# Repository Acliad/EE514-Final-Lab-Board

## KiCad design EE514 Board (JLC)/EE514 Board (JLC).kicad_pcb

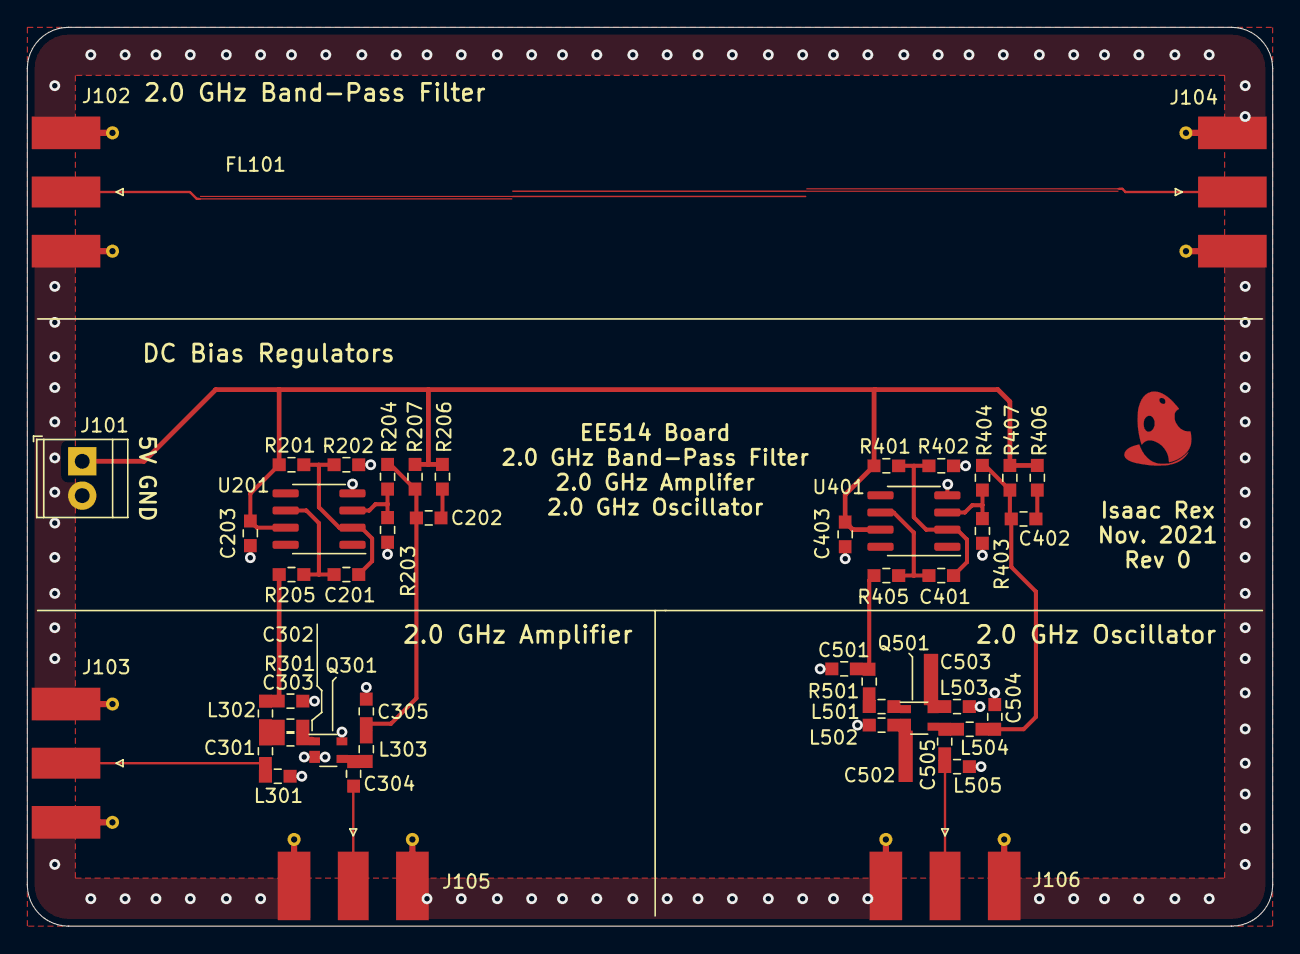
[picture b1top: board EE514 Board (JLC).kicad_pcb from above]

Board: 4 copper layers, 92.2 x 66.5 mm, 51 parts (0 on the bottom side), 27 nets.

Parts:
C201, C202, C401, C402: 12nF; C_0603_1608Metric_Pad0.98x0.95mm_HandSolder
C203, C403: 0.1uF; C_0603_1608Metric_Pad0.98x0.95mm_HandSolder
C301: 4.7pF; C_0603_1608Metric_Pad0.98x0.95mm_HandSolder
C302, C303, C305, C501, C504: 7.5pF; C_0603_1608Metric_Pad0.98x0.95mm_HandSolder
C304: 6.8pF; C_0603_1608Metric_Pad0.98x0.95mm_HandSolder
C502, C503: 1.7pF; C_1.7pF_Microstrip
C505: 3pF; C_0603_1608Metric_Pad0.98x0.95mm_HandSolder
FL101: BPF-2; Filter_2.0GHz_Bandpass_Edge-Coupled_JLC
J101: Screw_Terminal_01x02; TerminalBlock_TE_282834-2_1x02_P2.54mm_Horizontal
J102, J103, J104, J105, J106: SMA; SMA_Molex_73251-1153_EdgeMount_Horizontal
L301: 1.3nH; L_0603_1608Metric_Pad0.98x0.95mm_HandSolder
L302, L502, L503, L504: 18nH; L_0603_1608Metric_Pad0.98x0.95mm_HandSolder
L303: 1.8nH; L_0603_1608Metric_Pad0.98x0.95mm_HandSolder
L501: 6.2nH; L_0603_1608Metric_Pad0.98x0.95mm_HandSolder
L505: 2.2nH; L_0603_1608Metric_Pad0.98x0.95mm_HandSolder
Q301, Q501: BFP620; SOT-343_2.0x1.25mm_P1.3mm
R201, R401: 1.5k; R_0603_1608Metric_Pad0.98x0.95mm_HandSolder
R202, R402: 470; R_0603_1608Metric_Pad0.98x0.95mm_HandSolder
R203, R403: 11k; R_0603_1608Metric_Pad0.98x0.95mm_HandSolder
R204, R404: 7.5k; R_0603_1608Metric_Pad0.98x0.95mm_HandSolder
R205, R405: 3.3k; R_0603_1608Metric_Pad0.98x0.95mm_HandSolder
R206, R406: 18; R_0603_1608Metric_Pad0.98x0.95mm_HandSolder
R207, R407: 75; R_0603_1608Metric_Pad0.98x0.95mm_HandSolder
R301: 1; R_0603_1608Metric_Pad0.98x0.95mm_HandSolder
R501: 200; R_0603_1608Metric_Pad0.98x0.95mm_HandSolder
U201, U401: TLC2201; SOIC-8_3.9x4.9mm_P1.27mm

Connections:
+5V: C203.2, C403.2, J101.1, R201.1, R206.1, R207.1, R401.1, R406.1, R407.1, U201.7, U401.7
/Amplifier/RF_IN: C301.2, J103.1, L301.1
/Amplifier/RF_OUT: C304.1, J105.1
/Amplifier/V_BIAS_BASE: C302.2, L302.2, R205.1
/Amplifier/V_BIAS_COLLECTOR: C202.1, C305.2, L303.2, R204.1, R207.2
/Oscillator/RF_OUT: C505.1, J106.1, L505.1
/Oscillator/V_BASE_BIAS: C501.2, R405.1, R501.2
/Oscillator/V_BASE_COLLECTOR: C402.1, C504.2, L504.2, R404.1, R407.2
GND: C203.1, C302.1, C305.1, C403.1, C501.1, C504.1, J101.2, J102.2, J103.2, J104.2, J105.2, J106.2, L301.2, L502.2, L503.2, L505.2, Q301.2, Q301.4, R202.2, R203.2, R402.2, R403.2, U201.4, U401.4
unnamed: C201.1, R205.2, U201.6
unnamed: C201.2, R201.2, R202.1, U201.2
unnamed: C202.2, R206.2
unnamed: C301.1, C303.2, L302.1, R301.2
unnamed: C303.1, Q301.1, R301.1
unnamed: C304.2, L303.1, Q301.3
unnamed: C401.1, R405.2, U401.6
unnamed: C401.2, R401.2, R402.1, U401.2
unnamed: C402.2, R406.2
unnamed: C502.1, L502.1, Q501.2
unnamed: C503.1, L503.1, Q501.4
unnamed: C505.2, L504.1, Q501.3
unnamed: FL101.1, J102.1
unnamed: FL101.2, J104.1
unnamed: L501.1, R501.1
unnamed: L501.2, Q501.1
unnamed: R203.1, R204.2, U201.3
unnamed: R403.1, R404.2, U401.3

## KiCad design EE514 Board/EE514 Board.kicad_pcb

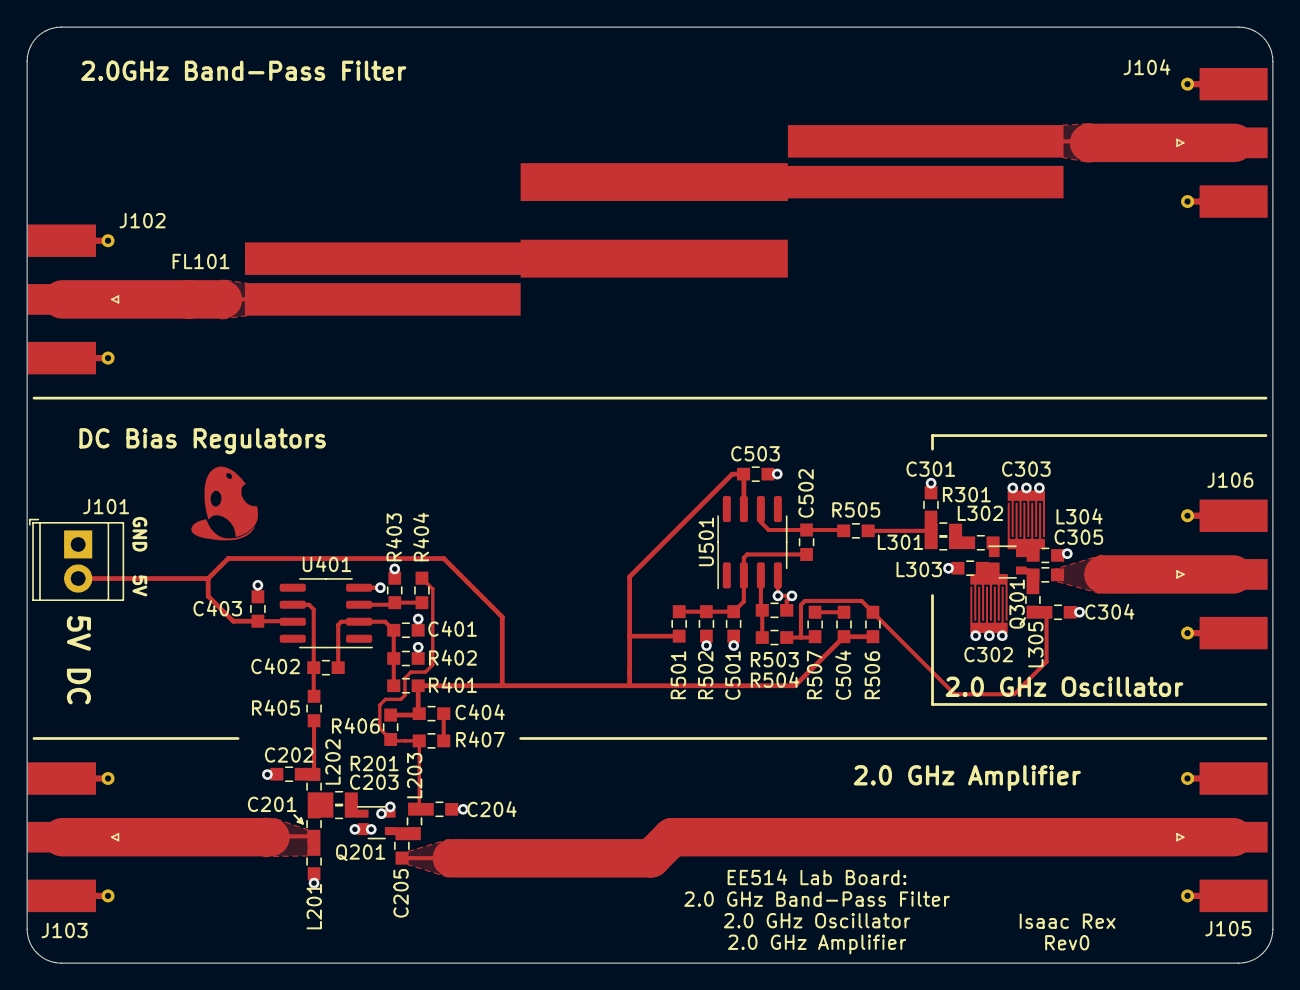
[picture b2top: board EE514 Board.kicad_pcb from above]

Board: 2 copper layers, 93.0 x 69.9 mm, 53 parts (0 on the bottom side), 27 nets.

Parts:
C201: 2.2pF; C_0603_1608Metric_Pad0.98x0.95mm_HandSolder
C202, C203, C204, C301, C304: 7.5pF; C_0603_1608Metric_Pad0.98x0.95mm_HandSolder
C205: 3.9pF; C_0603_1608Metric_Pad0.98x0.95mm_HandSolder
C302, C303: 1pF; C_1pF_Interdigital
C305: 3pF; C_0603_1608Metric_Pad0.98x0.95mm_HandSolder
C401, C403, C501, C503: 0.1nF; C_0603_1608Metric_Pad0.98x0.95mm_HandSolder
C402, C404, C502, C504: 12nF; C_0603_1608Metric_Pad0.98x0.95mm_HandSolder
FL101: BPF-2; Filter_2.0GHz_Bandpass_Edge-Coupled
J101: Screw_Terminal_01x02; TerminalBlock_TE_282834-2_1x02_P2.54mm_Horizontal
J102, J103, J104, J105, J106: SMA; SMA_Molex_73251-1153_EdgeMount_Horizontal
L201: 2.2nH; L_0603_1608Metric_Pad0.98x0.95mm_HandSolder
L202, L301, L303, L304: 18nH; L_0603_1608Metric_Pad0.98x0.95mm_HandSolder
L203: 3.9nH; L_0603_1608Metric_Pad0.98x0.95mm_HandSolder
L302: 7.5nH; L_0603_1608Metric_Pad0.98x0.95mm_HandSolder
L305: 8.2nH; L_0603_1608Metric_Pad0.98x0.95mm_HandSolder
Q201: BFP620; SOT-343_2.0x1.25mm_P1.3mm
Q301: BPF620; SOT-343_2.0x1.25mm_P1.3mm
R201: 1.5; R_0603_1608Metric_Pad0.98x0.95mm_HandSolder
R301: 150; R_0603_1608Metric_Pad0.98x0.95mm_HandSolder
R401, R501: 1.5k; R_0603_1608Metric_Pad0.98x0.95mm_HandSolder
R402, R502: 470; R_0603_1608Metric_Pad0.98x0.95mm_HandSolder
R403, R503: 11k; R_0603_1608Metric_Pad0.98x0.95mm_HandSolder
R404, R504: 7.4k; R_0603_1608Metric_Pad0.98x0.95mm_HandSolder
R405, R505: 3.3k; R_0603_1608Metric_Pad0.98x0.95mm_HandSolder
R406, R506: 75; R_0603_1608Metric_Pad0.98x0.95mm_HandSolder
R407, R507: 18; R_0603_1608Metric_Pad0.98x0.95mm_HandSolder
U401, U501: TLC2201; SOIC-8_3.9x4.9mm_P1.27mm

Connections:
+5V: C403.2, C404.2, C503.2, C504.2, J101.2, R401.1, R406.1, R501.1, R506.1, U401.7, U501.7
/Amplifier/RF_IN: C201.2, J103.1, L201.1
/Amplifier/RF_OUT: C205.1, J105.1
/Amplifier/V_BIAS_BASE: C202.1, L202.2, R405.1
/Amplifier/V_BIAS_COLLECTOR: C204.1, L203.2, R404.1, R406.2, R407.2
/Bias Regulator (Amplifier)/VREF_1.2V: C401.2, C402.2, R401.2, R402.1, U401.2
/Bias Regulator (Oscillator)/VREF_1.2V: C501.2, C502.2, R501.2, R502.1, U501.2
/Bias Regulator (Oscillator)/V_BIAS_BASE: C301.1, L301.2, R301.2, R505.1
/Bias Regulator (Oscillator)/V_BIAS_COLLECTOR: C304.1, L305.2, R504.1, R506.2, R507.2
/FILT_IN: FL101.1, J102.1
/FILT_OUT: FL101.2, J104.1
/Oscillator/RF_OUT: C305.1, J106.1
GND: C202.2, C204.2, C301.2, C302.2, C303.2, C304.2, C401.1, C403.1, C501.1, C503.1, J101.1, J102.2, J103.2, J104.2, J105.2, J106.2, L201.2, L303.2, L304.2, Q201.2, Q201.4, R402.2, R403.2, R502.2, R503.2, U401.4, U501.4
unnamed: C201.1, C203.2, L202.1, R201.2
unnamed: C203.1, Q201.1, R201.1
unnamed: C205.2, L203.1, Q201.3
unnamed: C302.1, L303.1, Q301.2
unnamed: C303.1, L304.1, Q301.4
unnamed: C305.2, L305.1, Q301.3
unnamed: C402.1, R405.2, U401.6
unnamed: C404.1, R407.1
unnamed: C502.1, R505.2, U501.6
unnamed: C504.1, R507.1
unnamed: L301.1, L302.2, R301.1
unnamed: L302.1, Q301.1
unnamed: R403.1, R404.2, U401.3
unnamed: R503.1, R504.2, U501.3

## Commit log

2021-11-19 Layout finished, updating silkscreen...
2021-11-19 Finished placing silkscreen
2021-11-19 Added silkscreen and logo
2021-11-19 Updated soldermask on interdigital cap, added silkscreen for DC terminal, updated gerbers
2021-11-24 Added JLC design
2021-11-25 Updated JLC board with edge fence and edge soldermask pullback
